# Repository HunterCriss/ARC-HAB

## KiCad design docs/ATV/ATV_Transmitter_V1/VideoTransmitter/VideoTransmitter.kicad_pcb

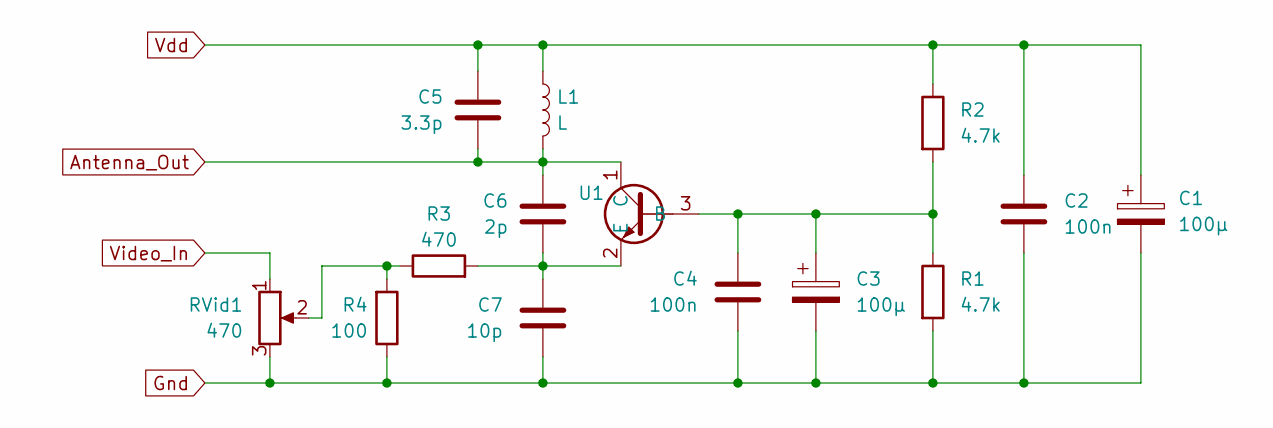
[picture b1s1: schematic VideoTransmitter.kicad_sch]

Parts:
C1, C3: 100µ; 100µF
C2, C4: 100n; 0.1uF
C5: 3.3p; 3.3pF
C6: 2p; 2pF
C7: 10p; 10pF
L1: L
R1, R2: 4.7k; 4.7kOhm
R3: 470; 470Ohm
R4: 100; 100Ohm
RVid1: 470; 470 Pot
U1: BFR91A NPN

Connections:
Antenna_Out: C5.2, C6.1, L1.2, U1.1 (C)
Gnd: C1.2, C2.2, C3.2, C4.2, C7.2, R1.2, R4.1, RVid1.3
unnamed: R3.1, R4.2, RVid1.2
unnamed: C3.1, C4.1, R1.1, R2.2, U1.3 (B)
unnamed: C6.2, C7.1, R3.2, U1.2 (E)
Vdd: C1.1, C2.1, C5.1, L1.1, R2.1
Video_In: RVid1.1

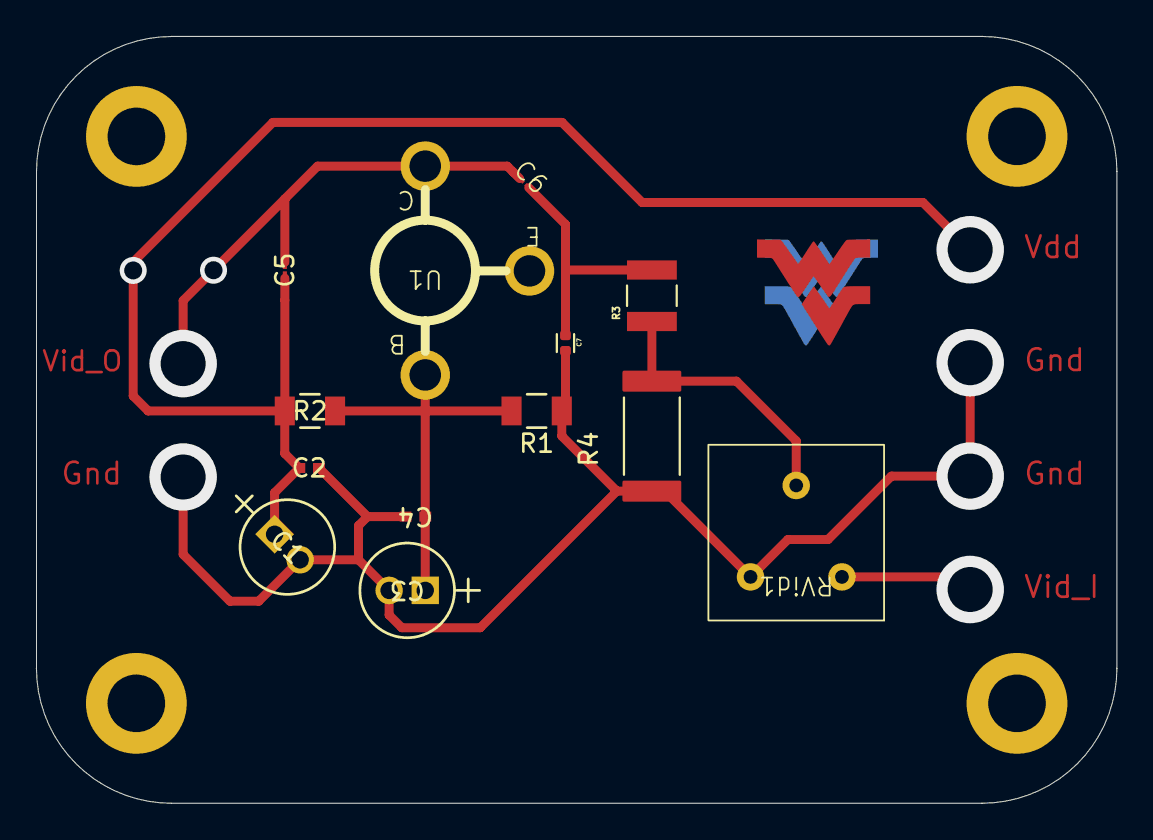
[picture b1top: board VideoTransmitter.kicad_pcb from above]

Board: 2 copper layers, 60.0 x 42.6 mm, 13 parts (0 on the bottom side), 6 nets.

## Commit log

2024-12-07 ATV KiCad
